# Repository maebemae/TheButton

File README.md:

# THE BUTTON

This project aims to solve a key issue of the everyday programmer - how to safely, reliably, and in a repeatable fashion provide good feedback.

# Demonstration

[Youtube Video](https://www.youtube.com/shorts/mlwx9P0IeXQ) showing the button in action

# Using the configurator

The button will open a com port on your machine.

To configure, simply connect to it with 115200 baud rate, and follow the instructions. Do not forget to save the new settings by writing to flash, else they will be lost after a power cycle.

(On mac typically /dev/tty.usbmodem00011, on linux /dev/tty.ACME0) 
If not sure, open the com port listing (i.e. ls /dev/tty, or check the list in windows, connect the button, and see what changed)

If you have chrome, you can navigate to https://www.serialterminal.com/index.html
Or else you can use screen, minicom, or any other com 

This could be as simple as `screen /dev/tty.usbmodem00011`. To disconnect, just unplug the button

# Flashing the firmware
## Using USB DFU

1. Put The Button into DFU mode, either by
	a. Fully pressing the button and then plugging it in, or
	b. Pressing the 'boot' button and then plugging it in
2. You can use the [STM32CubeProgrammer](https://www.st.com/en/development-tools/stm32cubeprog.html) or [DfuSe](https://www.st.com/en/development-tools/stsw-stm32080.html)
3. Select USB Connection, and refresh the Port Necessarily. If you have sucessfully put your device into DFU mode, you will now see USB1 (or similar number) in the ports
4. Click connect
5. Switch to the 'Erasing & Programming' Section, load the firmware file path, and
6. Start programming
7. Disconnect and Reconnect The Button 

# Hardware

I've selected the STM32C071 as it has crystalless USB, is affordable with sufficient Flash, RAM and GPIO for potential extensions. It also has affordable dev kit [STM32 nucleo-c071rb](https://www.st.com/en/evaluation-tools/nucleo-c071rb.html) at $10 with USB-C.

Designed with Kicad, can be found under /pcb

The schematic and gerbers can be found under /pcb/output/

## KNOWN BUGS
1. The debug header silkscreen is reversed (gnd/3v3!)

# Firmware

The project is built with [STM32CubeIde](https://www.st.com/en/development-tools/stsw-stm32080.html)

Main entrypoint can be found at `The Buttoner/Core/Src/main` \
This is where the initialization generated by the STM32CubeMx IOC project happens,and also where we actually process the inputs

The second point is in `The Buttoner/libs/gbmUSBdevice/USBdev/Src/usb_app.c`, this is where we have the polled hook `HIDUpdateKB` which actually does the writing out to usb 

The gbmUSBdevice library was slightly altered and linked into the project. See [gbmUSBdevice](https://github.com/gbm-ii/gbmUSBdevice) for more details.

# Todo

1. Hardware
	1. [Not necessary] Add optional eeprom
	1. [DONE] Add hardware revision selector pins
	1. Add USB vid/pid selector (or do we just leave this in firmware?
	1. Add OpenHardware Logo 
	1. Fix the debug header silkscreen

1. Firmware
	1. [In progress] Add ondemand VCP to configure messages
	1. Apply for dedicated vid/pid from openmoko
	1. Cleanup startup so that button doesn't send messages when connected to usb

1. Project
	1. Cleanup structure 
	1. Tag versions

# License
The project in it's entirety is released under GNU GPL V3, a copy of which can be found in ./LICENSE

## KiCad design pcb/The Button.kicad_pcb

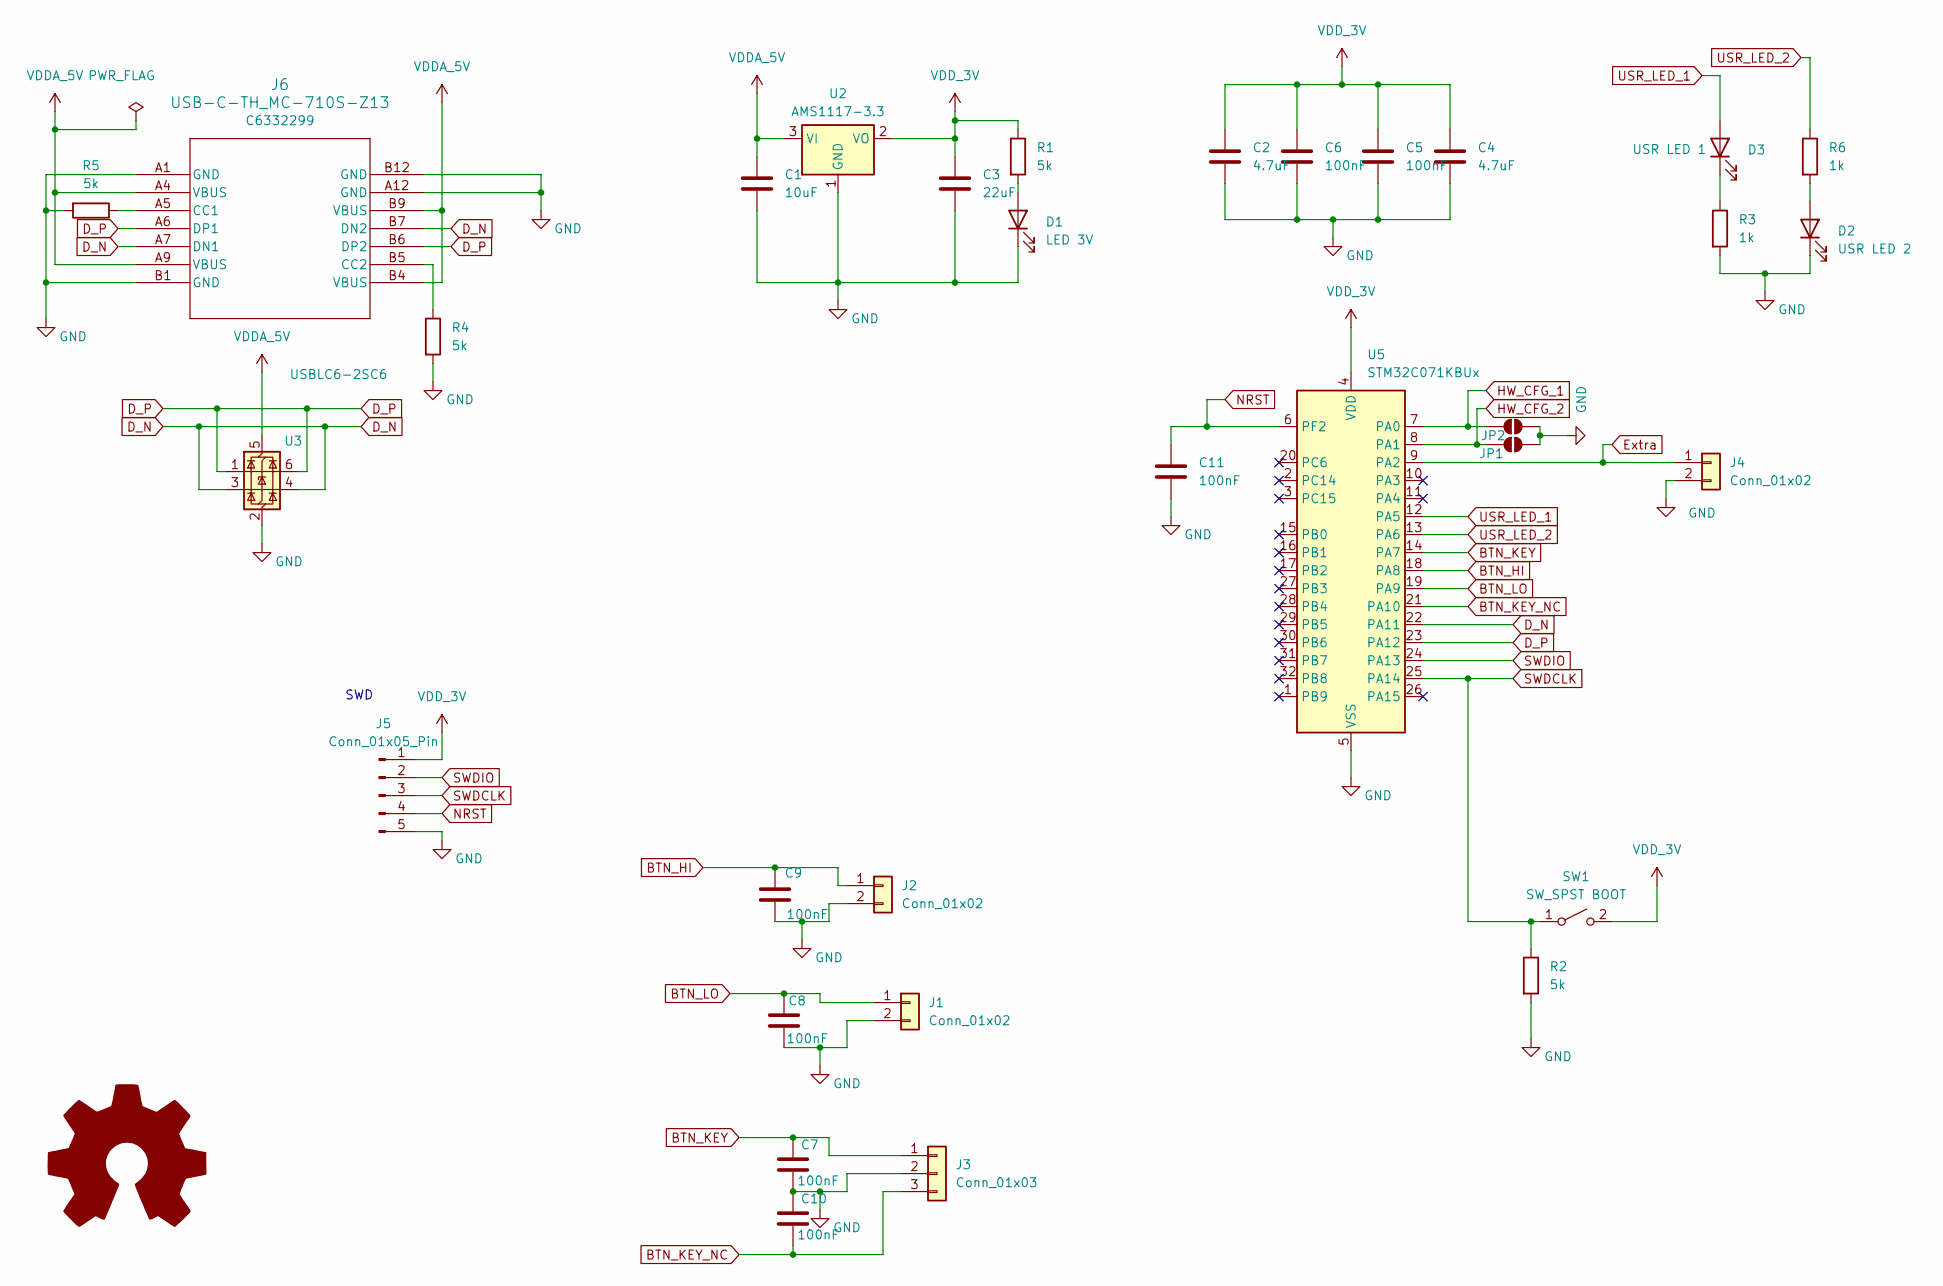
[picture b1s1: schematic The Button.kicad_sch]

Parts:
C1: 10uF; C_0805_2012Metric_Pad1.18x1.45mm_HandSolder
C2, C4: 4.7uF; C_0805_2012Metric_Pad1.18x1.45mm_HandSolder
C3: 22uF; C_0805_2012Metric_Pad1.18x1.45mm_HandSolder
C5, C6, C7, C8, C9, C10, C11: 100nF; C_0805_2012Metric_Pad1.18x1.45mm_HandSolder
D1: LED 3V; LED_0805_2012Metric_Pad1.15x1.40mm_HandSolder
D2: USR LED 2; LED_0805_2012Metric_Pad1.15x1.40mm_HandSolder
D3: USR LED 1; LED_0805_2012Metric_Pad1.15x1.40mm_HandSolder
J1, J2: Conn_01x02; JST_XH_B2B-XH-AM_1x02_P2.50mm_Vertical
J3: Conn_01x03; JST_XH_B3B-XH-AM_1x03_P2.50mm_Vertical
J4: Conn_01x02; PinHeader_1x02_P2.54mm_Vertical
J5: Conn_01x05_Pin; PinSocket_1x05_P2.54mm_Vertical
J6: USB-C-TH_MC-710S-Z13; USB_THT_SIDE_INSERT_14P; LCSC C6332299
JP1, JP2: SolderJumper_2_Open; SolderJumper-2_P1.3mm_Open_TrianglePad1.0x1.5mm
R1, R2, R4, R5: 5k; R_0805_2012Metric_Pad1.20x1.40mm_HandSolder
R3, R6: 1k; R_0805_2012Metric_Pad1.20x1.40mm_HandSolder
SW1: SW_SPST BOOT; SW_PUSH_SPST_3X3MM; LCSC C5143623
U2: AMS1117-3.3; SOT-89-3
U3: USBLC6-2SC6; SOT-23-6
U5: STM32C071KBUx; QFN-32-1EP_5x5mm_P0.5mm_EP3.45x3.45mm

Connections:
BTN_HI: C9.1, J2.1, U5.18 (PA8)
BTN_KEY: C7.1, J3.1, U5.14 (PA7)
BTN_KEY_NC: C10.2, J3.3, U5.21 (PA10)
BTN_LO: C8.1, J1.1, U5.19 (PA9)
D_N: J6.A7 (DN1), J6.B7 (DN2), U3.3 (I/O2), U3.4 (I/O2), U5.22 (PA11)
D_P: J6.A6 (DP1), J6.B6 (DP2), U3.1 (I/O1), U3.6 (I/O1), U5.23 (PA12)
Extra: J4.1, U5.9 (PA2)
GND: C1.2, C2.2, C3.2, C4.2, C5.2, C6.2, C7.2, C8.2, C9.2, C10.1, C11.2, D1.1 (K), D2.1 (K), J1.2, J2.2, J3.2, J4.2, J5.5, J6.A1 (GND), J6.A12 (GND), J6.B1 (GND), J6.B12 (GND), JP1.1 (A), JP2.1 (A), R2.2, R3.2, R4.2, R5.2, U2.1 (GND), U3.2 (GND), U5.5 (VSS), U5.33 (VSS)
HW_CFG_1: JP2.2 (B), U5.7 (PA0)
HW_CFG_2: JP1.2 (B), U5.8 (PA1)
NRST: C11.1, J5.4, U5.6 (PF2)
unnamed: D1.2 (A), R1.2
unnamed: D2.2 (A), R6.2
unnamed: D3.1 (K), R3.1
unnamed: J6.A5 (CC1), R5.1
unnamed: J6.B5 (CC2), R4.1
SWDCLK: J5.3, R2.1, SW1.1 (A), U5.25 (PA14)
SWDIO: J5.2, U5.24 (PA13)
USR_LED_1: D3.2 (A), U5.12 (PA5)
USR_LED_2: R6.1, U5.13 (PA6)
VDDA_5V: C1.1, J6.A4 (VBUS), J6.A9 (VBUS), J6.B4 (VBUS), J6.B9 (VBUS), U2.3 (VI), U3.5 (VBUS)
VDD_3V: C2.1, C3.1, C4.1, C5.1, C6.1, J5.1, R1.1, SW1.2 (B), U2.2 (VO), U5.4 (VDD)

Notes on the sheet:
SWD

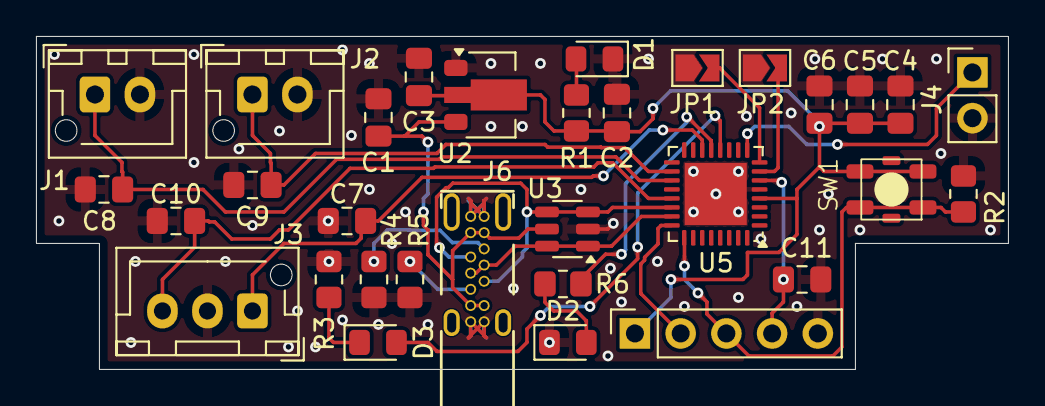
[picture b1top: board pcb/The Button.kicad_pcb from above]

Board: 2 copper layers, 54.0 x 18.5 mm, 32 parts (0 on the bottom side), 22 nets.

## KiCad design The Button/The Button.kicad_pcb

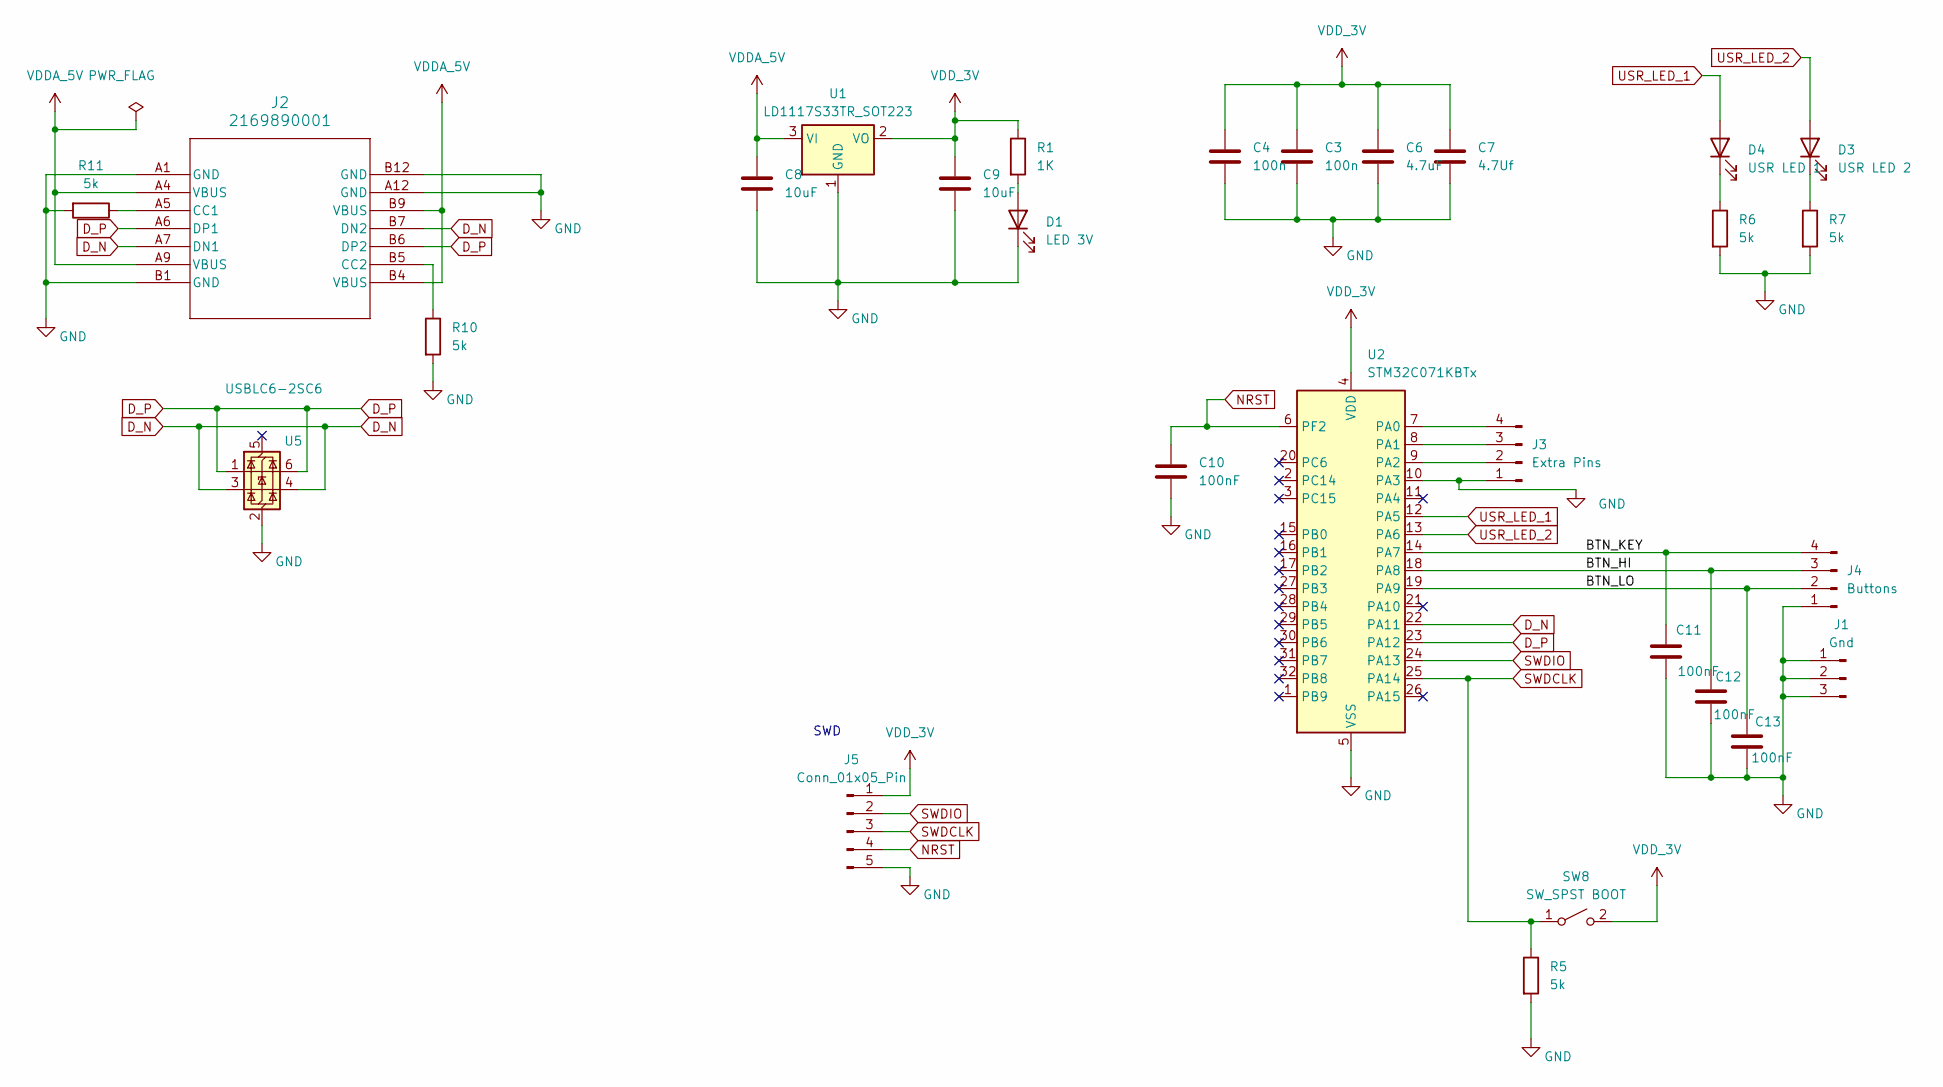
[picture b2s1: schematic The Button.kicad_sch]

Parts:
C3, C4: 100n; C_0805_2012Metric_Pad1.18x1.45mm_HandSolder
C6: 4.7uF; C_0805_2012Metric_Pad1.18x1.45mm_HandSolder
C7: 4.7Uf; C_0805_2012Metric_Pad1.18x1.45mm_HandSolder
C8, C9: 10uF; C_0805_2012Metric_Pad1.18x1.45mm_HandSolder
C10, C11, C12, C13: 100nF; C_0805_2012Metric_Pad1.18x1.45mm_HandSolder
D1: LED 3V; LED_0805_2012Metric_Pad1.15x1.40mm_HandSolder
D3: USR LED 2; LED_0805_2012Metric_Pad1.15x1.40mm_HandSolder
D4: USR LED 1; LED_0805_2012Metric_Pad1.15x1.40mm_HandSolder
J1: Gnd; PinSocket_1x03_P2.54mm_Vertical
J2: 2169890001; 216989-0001_MOL
J3: Extra Pins; PinSocket_1x04_P2.54mm_Vertical
J4: Buttons; PinSocket_1x04_P2.54mm_Vertical
J5: Conn_01x05_Pin; PinSocket_1x05_P2.54mm_Vertical
R1: 1K; R_0805_2012Metric_Pad1.20x1.40mm_HandSolder
R5, R6, R7, R10, R11: 5k; R_0805_2012Metric_Pad1.20x1.40mm_HandSolder
SW8: SW_SPST BOOT; SW_SPST_FSMSM
U1: LD1117S33TR_SOT223; SOT-223-3_TabPin2
U2: STM32C071KBTx; LQFP-32_7x7mm_P0.8mm
U5: USBLC6-2SC6; SOT-23-6

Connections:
/BTN_HI: C12.1, J4.3, U2.18 (PA8)
/BTN_KEY: C11.1, J4.4, U2.14 (PA7)
/BTN_LO: C13.1, J4.2, U2.19 (PA9)
D_N: J2.A7 (DN1), J2.B7 (DN2), U2.22 (PA11), U5.3 (I/O2), U5.4 (I/O2)
D_P: J2.A6 (DP1), J2.B6 (DP2), U2.23 (PA12), U5.1 (I/O1), U5.6 (I/O1)
GND: C3.2, C4.2, C6.2, C7.2, C8.2, C9.2, C10.2, C11.2, C12.2, C13.2, D1.1 (K), J1.1, J1.2, J1.3, J2.A1 (GND), J2.A12 (GND), J2.B1 (GND), J2.B12 (GND), J3.1, J4.1, J5.5, R5.2, R6.2, R7.2, R10.2, R11.2, U1.1 (GND), U2.5 (VSS), U2.10 (PA3), U5.2 (GND)
NRST: C10.1, J5.4, U2.6 (PF2)
unnamed: D1.2 (A), R1.2
unnamed: D3.1 (K), R7.1
unnamed: D4.1 (K), R6.1
unnamed: J2.A5 (CC1), R11.1
unnamed: J2.B5 (CC2), R10.1
unnamed: J3.2, U2.9 (PA2)
unnamed: J3.3, U2.8 (PA1)
unnamed: J3.4, U2.7 (PA0)
SWDCLK: J5.3, R5.1, SW8.1 (A), U2.25 (PA14)
SWDIO: J5.2, U2.24 (PA13)
USR_LED_1: D4.2 (A), U2.12 (PA5)
USR_LED_2: D3.2 (A), U2.13 (PA6)
VDDA_5V: C8.1, J2.A4 (VBUS), J2.A9 (VBUS), J2.B4 (VBUS), J2.B9 (VBUS), U1.3 (VI)
VDD_3V: C3.1, C4.1, C6.1, C7.1, C9.1, J5.1, R1.1, SW8.2 (B), U1.2 (VO), U2.4 (VDD)

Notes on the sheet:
SWD

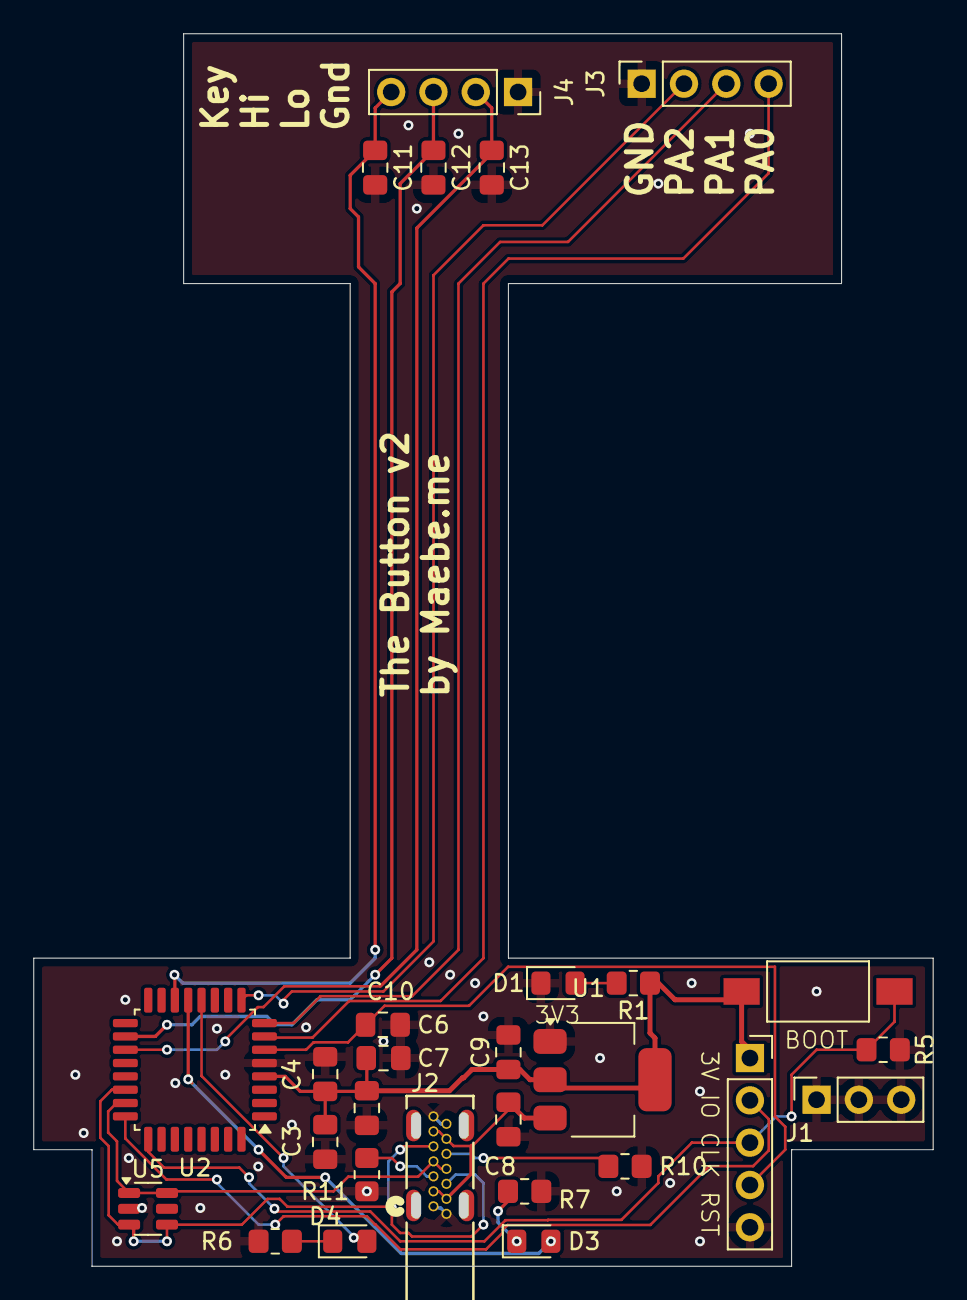
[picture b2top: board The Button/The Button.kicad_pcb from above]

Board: 2 copper layers, 53.4 x 73.4 mm, 28 parts (0 on the bottom side), 21 nets.

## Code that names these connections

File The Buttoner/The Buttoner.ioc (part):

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Mcu.Name=STM32C071RBTx
Mcu.Package=LQFP64_GP
Mcu.UserName=STM32C071RBTx
PA11\ [PA9].Mode=Device
PA11\ [PA9].Signal=USB_DM
PA12\ [PA10].Mode=Device
PA12\ [PA10].Signal=USB_DP
PA13.Mode=Serial_Wire
PA13.Signal=DEBUG_SWDIO
PA14-BOOT0.Mode=Serial_Wire
PA14-BOOT0.Signal=DEBUG_SWCLK
PA2.GPIOParameters=GPIO_PuPd,GPIO_Label,GPIO_ModeDefaultEXTI
PA2.GPIO_Label=KEY_SWITCH_LED
PA2.GPIO_ModeDefaultEXTI=GPIO_MODE_IT_RISING
PA2.GPIO_PuPd=GPIO_PULLUP
PA2.Signal=GPXTI2
PA5.Signal=GPIO_Output
PA6.GPIOParameters=GPIO_Label
PA6.GPIO_Label=USR_LED2
PA6.Signal=GPIO_Output
PA7.GPIOParameters=GPIO_PuPd,GPIO_Label,GPIO_ModeDefaultEXTI
PA7.GPIO_Label=KEY_SWITCH
PA7.GPIO_ModeDefaultEXTI=GPIO_MODE_IT_RISING_FALLING
PA7.GPIO_PuPd=GPIO_PULLUP
PA7.Signal=GPXTI7
PA8.GPIOParameters=GPIO_PuPd,GPIO_Label,GPIO_ModeDefaultEXTI
PA8.GPIO_Label=BUTTON_LO
PA8.GPIO_ModeDefaultEXTI=GPIO_MODE_IT_RISING_FALLING
PA8.GPIO_PuPd=GPIO_PULLUP
PA8.Signal=GPXTI8
PA9\ [PA11].GPIOParameters=GPIO_PuPd,GPIO_Label,GPIO_ModeDefaultEXTI
PA9\ [PA11].GPIO_Label=BUTTON_HI
PA9\ [PA11].GPIO_ModeDefaultEXTI=GPIO_MODE_IT_RISING_FALLING
PA9\ [PA11].GPIO_PuPd=GPIO_PULLUP
PA9\ [PA11].Signal=GPXTI9
PC13.Signal=GPIO_Input
PC9.Signal=GPIO_Output
RCC.HSE_VALUE=8000000
RCC.SYSCLKFreq_VALUE=12000000
board=NUCLEO-C071RB
boardIOC=true

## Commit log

2024-12-23 Initial, got working usb hid example from gbmUSBDevice; also got button interrupts working (disabled)
2024-12-23 Add gitignore
2024-12-23 Apply gitignore
2024-12-23 Inline dependent library
2024-12-23 Add libs
2024-12-23 Working string shifting
2024-12-23 The use the external button
2024-12-23 Drop debug listing
2024-12-23 Drop silly files
2024-12-25 Adding kicad layouts
2024-12-27 Move character conversion to separate file
2024-12-27 Working newline
2024-12-27 Completed hid converter
2024-12-27 Measuring something!
2024-12-30 Timer nicely debounced
2024-12-30 debounced
2024-12-30 Enabled flash and still works
2024-12-30 timing still works
2024-12-30 It fucks
2024-12-30 Working texts
2024-12-30 Safe insults
2024-12-30 Enable DFU
2024-12-30 Can read from flash
2024-12-30 Can write some flash yay
2024-12-30 Disable leds on startup
2025-01-01 Bootloader on button press
2025-01-01 Add LEDs
2025-01-03 Disable 1 cdc channel and some optimizations
2025-01-04 Enterprise compliant button
2025-01-08 Execute write even on gentle press
2025-01-08 Clean up project structure
2025-01-08 Add demonstration
2025-01-09 Add missing files
2025-01-11 Update LICENSE
    Change to properly formatted
2025-01-11 Check in schematic
2025-01-11 Add the files
2025-01-11 Starting VCP menu
2025-01-11 Initial vcp menu
2025-01-11 Fix message too long
2025-01-11 Slowly building it up
2025-01-12 Move messages into struct
2025-01-12 Can write to flash, but there's an error
2025-01-12 Can edit messages
2025-01-12 Working configurator
2025-01-12 Disable debugs
2025-01-12 Worksss
2025-01-16 Update pcb schematic to v3, layout pending
2025-01-17 Routing of pcb v3
2025-01-17 Added solder jumpers for hw config
2025-01-17 Some minor tweaks, bump to v4
2025-01-18 Cleanup
2025-01-18 Working on looonix and correctly default if flash is 'corrupted'
2025-01-29 Generated new boms
2025-01-29 Fix issues with some micros setding the same message multiple times randomyl
2025-01-29 udpate readme
2025-01-30 Cleanup cyclo files
2025-01-30 Add in printed schematic
2025-01-30 Reformat pcb layout and update readme
2025-01-30 Add license link
2025-01-30 Add configurator instructions tto readme
2025-01-30 No longer printing on connection
2025-04-17 Updating for fabrication with jlcpcb
2025-04-17 Update gitignore
2025-04-23 Redesigned and rerouted
2025-04-24 Fixed to use correct MCU - STM32*C*071, not L
